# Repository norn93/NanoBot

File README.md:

# ANDRIS - AutoNomous Driving Robotic Interactive System: An Open-source Arduino Nano based Robot 

ANDRIS is an educational platform for highschool and university students to use to learn about robot hardware and software.

* Deprecated: Old files tagged for deletion
* Hardware: KiCad PCB designs and libraries
* Libraries: Contains the most up to date versions of the different libraries we use
	* Debug: Library for debugging code, and for testing
	* NanoBot: The current official release
* Results: Part of our ongoing debugging and testing for the library
* Programs: Contains some example programs which make use of the NanoBot library
	* robot_move_commands: A basic sketch for Alfie. Control the robot via bluetooth and keyboard. 

## Hardware todo:
* Revise PCB to version 1.0
	
## Software todo:
* Edit library: it should only include the bare minimum it needs to function, and it should be commented clearly

## Authors
* **George Knowlden** - Initial work, PCB design
* **Kimberley Siew** - Initial work, PCB design
* **Ashwin D'Cruz** - Initial work

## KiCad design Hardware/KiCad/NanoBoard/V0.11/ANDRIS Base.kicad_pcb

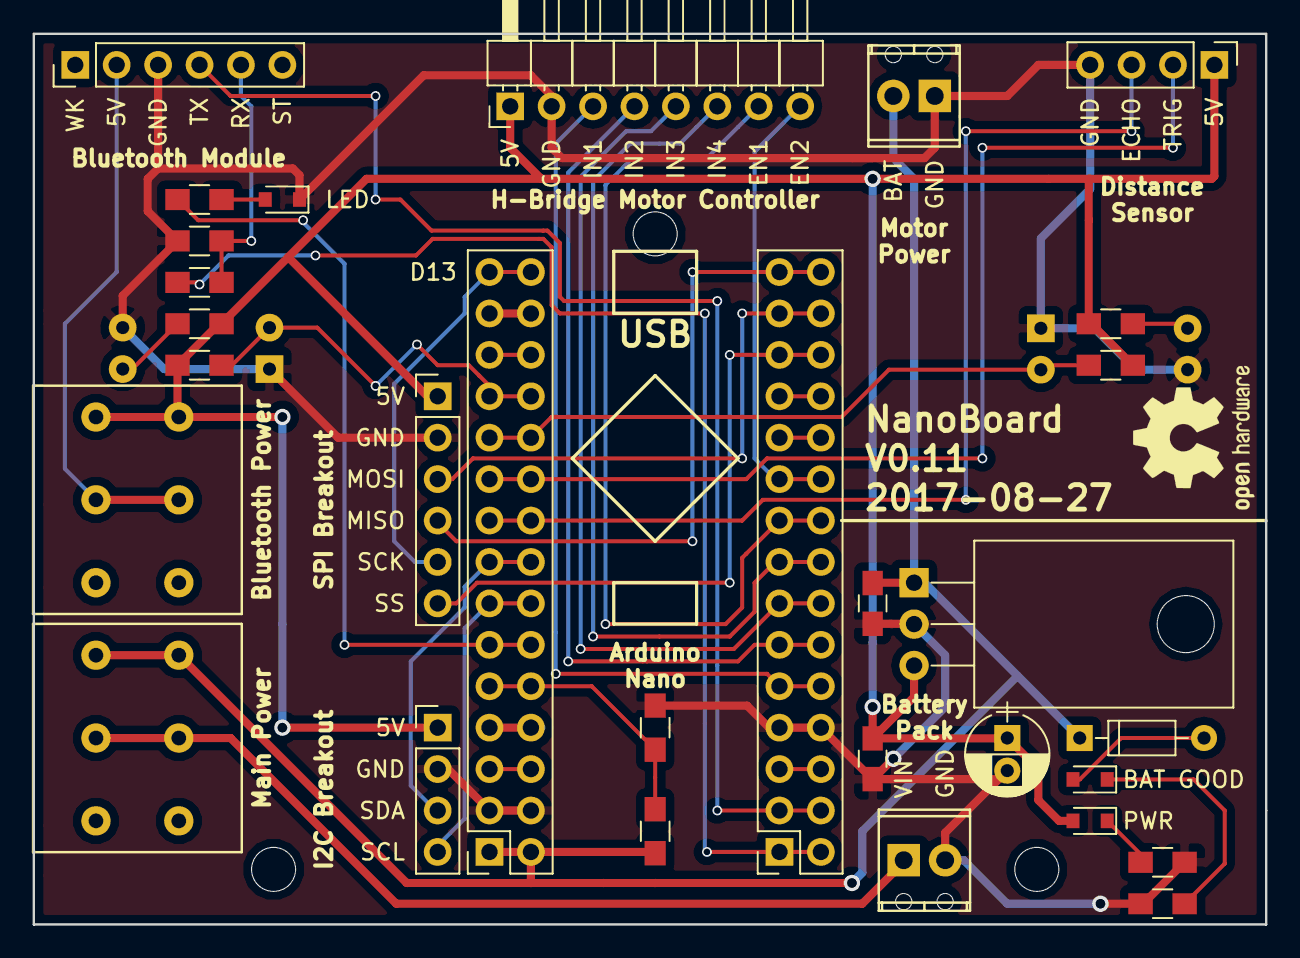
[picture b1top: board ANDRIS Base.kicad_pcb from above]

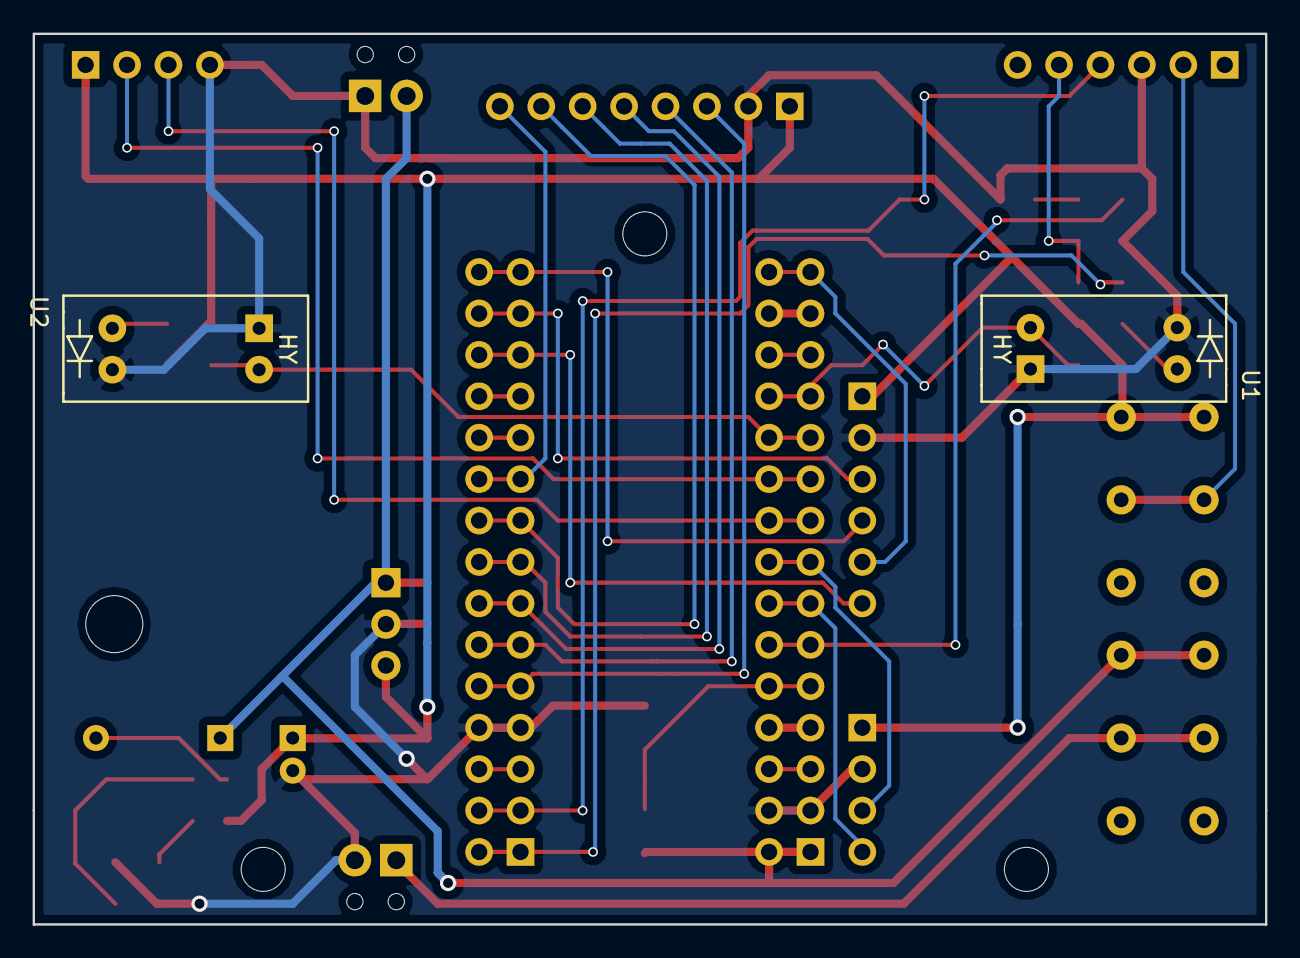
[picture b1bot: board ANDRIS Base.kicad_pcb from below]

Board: 2 copper layers, 75.6 x 54.6 mm, 32 parts (2 on the bottom side), 38 nets.

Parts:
C1, C2: 1u; C_0805_HandSoldering
C3: 10u; CP_Radial_D5.0mm_P2.00mm
D1: PWR; D_0805
D2: 5V1; D_DO-35_SOD27_P7.62mm_Horizontal
D3, D4: LED; D_0805
P1: H-Bridge Connector; Pin_Header_Angled_1x08_Pitch2.54mm
P2: Ultransonic Transducer; Pin_Header_Straight_1x04_Pitch2.54mm
P3: Battery Pack Connection; TerminalBlock_RS_Pro_MPT-2.54mm_2pol
P4: Nano Left; Socket_Strip_Straight_2x15_Pitch2.54mm
P5: Nano Right; Socket_Strip_Straight_2x15_Pitch2.54mm
P6: I2C Breakout; Socket_Strip_Straight_1x04_Pitch2.54mm
P7: HC-05 Bluetooth Connection; Socket_Strip_Straight_1x06_Pitch2.54mm
P8: SPI Breakout; Socket_Strip_Straight_1x06_Pitch2.54mm
P9: Motor Connection; TerminalBlock_RS_Pro_MPT-2.54mm_2pol
R1, R3, R7, R10, R11: 220R; R_0805_HandSoldering
R2, R4, R6: 1k; R_0805_HandSoldering
R5: 2.2k; R_0805_HandSoldering
R8, R9: 10K; R_0805_HandSoldering
SW1, SW2: SW_DPDT; Dailywell_DPDT_Switch
U1: Left Optocoupler; LTH-301-07
U2: Right Optocoupler; LTH-301-07
U3: 7805; TO-220_Horizontal_FIXED

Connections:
+5V: C2.1, C3.1, D1.2, P1.1, P2.1, P6.1, P8.1, R1.2, R2.2, R3.2, R4.2, SW2.1, SW2.4, U3.VO
/3V3: P5.27, P5.28
/5V: P5.7, P5.8
/A0_OPT_L: P5.23, P5.24, R2.1, U1.16
/A1_OPT_R: P5.21, P5.22, R4.1, U2.16
/A2_UT_TRIG: P2.2, P5.19, P5.20
/A3_UT_ECHO: P2.3, P5.17, P5.18
/A4_SDA: P5.15, P5.16, P6.3
/A5_SCL: P5.13, P5.14, P6.4
/A6_LED: P5.11, P5.12, R10.1
/A7_BATTERY: P5.9, P5.10, R8.2, R9.1
/BAT: C1.1, D2.1, P5.1, P5.2, P9.2, R8.1, SW1.1, SW1.4, U3.VI
/BAT-SW: P3.1, SW1.2, SW1.5
/D2_IN1: P1.3, P4.9, P4.10
/D3_IN2: P1.4, P4.11, P4.12
/D4_IN3: P1.5, P4.13, P4.14
/D5_IN4: P1.6, P4.15, P4.16
/D6_EN1: P1.7, P4.17, P4.18
/D7_EN2: P1.8, P4.19, P4.20
/D8: P4.21, P4.22
/D9: P4.23, P4.24
/D10_SS: P4.25, P4.26, P8.6
/D11_MOSI: P4.27, P4.28, P8.3
/D12_MISO: P4.29, P4.30, P8.4
/D13_SCK: P5.29, P5.30, P8.5
/REF: P5.25, P5.26
/RST: P4.5, P4.6, P5.5, P5.6
/RX: P4.3, P4.4, P7.4
/SW-BT: P7.2, SW2.2, SW2.5
/TX: P4.1, P4.2, R6.2
GND: C1.2, C2.2, C3.2, D4.1, P1.2, P2.4, P3.2, P4.7, P4.8, P5.3, P5.4, P6.2, P7.3, P8.2, P9.1, R5.1, R7.1, R9.2, R11.2, U1.2, U1.15, U2.2, U2.15, U3.GND
unnamed: D1.1, R7.2
unnamed: D2.2, D3.2
unnamed: D3.1, R11.1
unnamed: D4.2, R10.2
unnamed: P7.5, R5.2, R6.1
unnamed: R1.1, U1.1
unnamed: R3.1, U2.1

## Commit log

2016-03-19 initial files
2016-03-19 adding arduino code
2016-03-19 Added debug .cpp with encoder debug
2016-03-19 commenting
2016-03-19 Separte debug.h now
2016-03-19 added move commands
2016-03-19 started work on speed calcs
2016-03-19 Cleaning up folder
2016-03-19 fixes for header file
2016-03-19 Changes to robot movement
2016-03-25 Added a .bat file that'll update the libraries properly
2016-03-25 Added the Debug library update to the .bat file as well
2017-02-25 testing git skills
2017-02-25 updating README
2017-02-25 Added hardware todo list
2017-02-25 added software todo
2017-02-25 changed to 'hardware todo'
2017-02-25 added 'a'
2017-02-25 added B
2017-02-25 try again learning git
2017-02-25 man this is annoying
2017-02-25 added a again
2017-02-25 adding b again
2017-02-25 started a help file for Git
2017-02-25 edited Git help file
2017-02-25 updating githelp
2017-02-25 made more changes to the githelp.txt
2017-02-25 sorting this out once and for all
2017-02-25 typo
2017-02-25 added line
2017-02-25 added a good example for merging
2017-02-25 made a change
2017-02-25 added line againnnn
2017-02-25 minor changes to the help file
2017-03-17 Added a workflow guide for Git
2017-03-25 Deleted useless file
2017-03-25 added line to Sotware todo
2017-03-25 Fixed merge conflicts in README
2017-03-25 Updated workflow
2017-03-25 Updating README to include motherboard manufacture
2017-03-25 fixed merge again
2017-03-25 Updated stlye of README.md
2017-03-25 Reorganised folder, and updated README
2017-03-25 Updated README to include more detail
2017-03-25 Updated README to include the deprecated folder
2017-03-25 Added KiCad files, updated README
2017-03-25 Update README to include hardware folder
2017-03-28 Testing commit from other PC
2017-04-01 Added a testing program
2017-04-01 Added some SoftwareSerial testing files
2017-04-01 Updated repo name
2017-04-01 Fixed typo
2017-04-29 Commented out _Nano_debug_print_encoder_left variable, added speed test results
2017-04-30 Added python script to estimate speed for a given deltaT
2017-05-06 made updates to the python movement analysis file
2017-05-06 Updated the README
    Better reflect current situation
2017-05-06 Updating tests
    Starting to compare the velocity estimates a little more accurately
2017-08-28 Added latest PCB files
2017-10-04 Updated program for version 0.11 of the board
2017-10-04 Updated library with new and improved NanoDrive command
2017-10-04 Updated README to reflect hardware changes
2017-10-04 Cleaned up code
2017-10-04 Added new program for testing the encoders
2017-10-05 Moved old debugging code into bin
2017-10-05 Small changes to library
2017-10-05 Small change to adjust to new library
2017-10-05 Small changes
2017-10-05 Failed attempt to illustrate problem with the code
2017-10-05 Failed attempt to put the library into a class
2017-10-05 Deletion of old/useless files
2017-10-06 Slight modifications for my sanity
2017-10-06 Redesign of library, pending function/variable name updates
